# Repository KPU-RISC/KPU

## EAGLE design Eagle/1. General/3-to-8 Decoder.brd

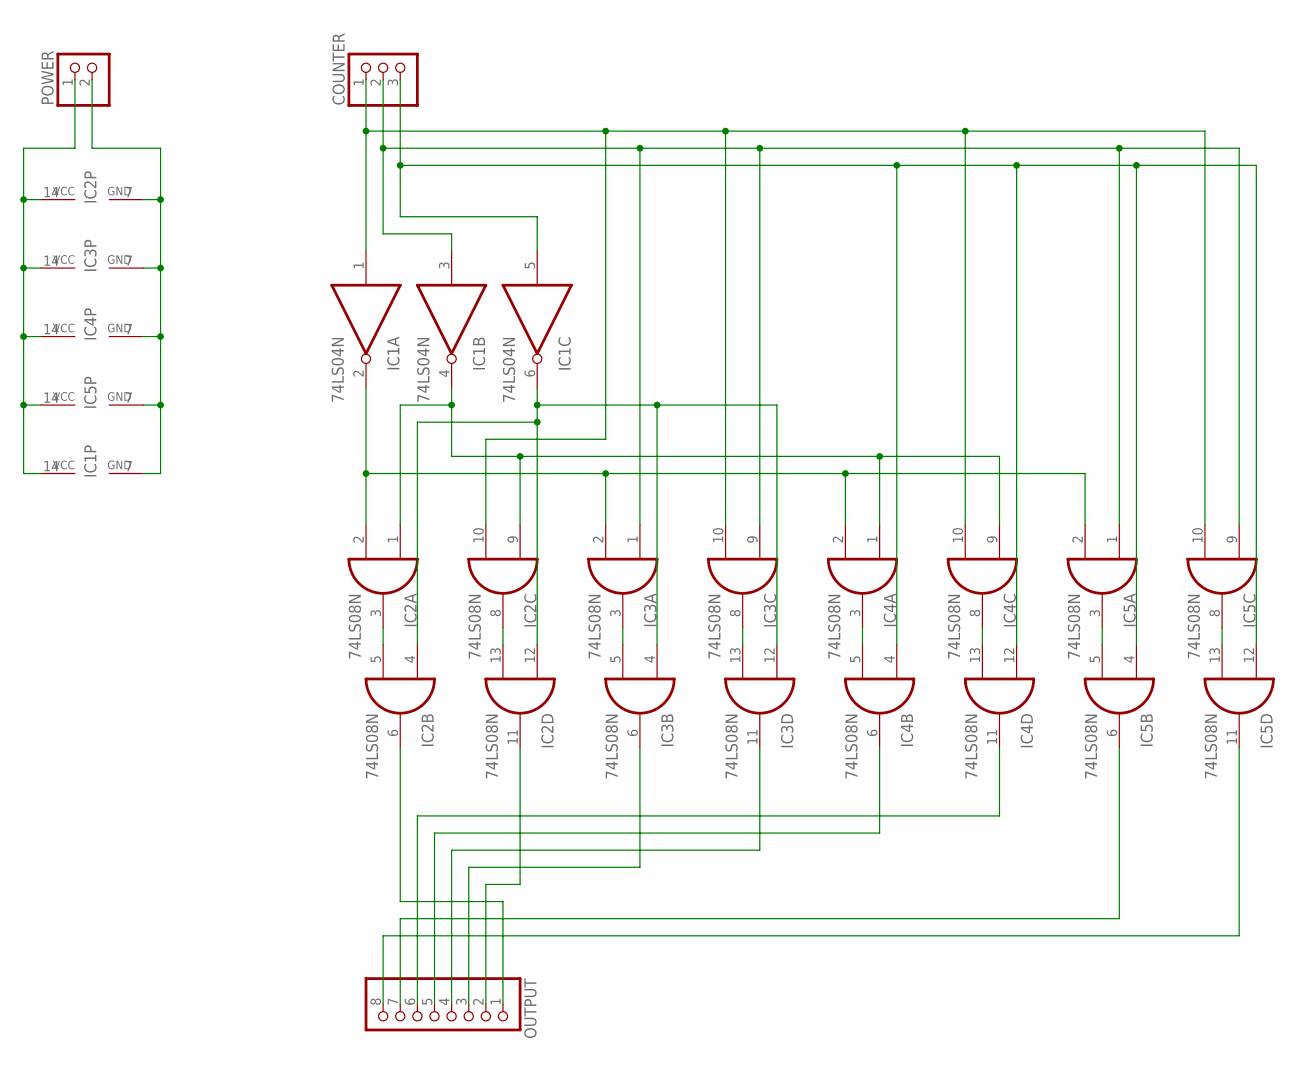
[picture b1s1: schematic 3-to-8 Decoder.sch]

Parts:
COUNTER: PINHD-1X3; 1X03
IC1: 74LS04N; DIL14
IC2, IC3, IC4, IC5: 74LS08N; DIL14
OUTPUT: PINHD-1X8; 1X08
POWER: PINHD-1X2; 1X02

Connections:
GND: IC1.7 (GND), IC2.7 (GND), IC3.7 (GND), IC4.7 (GND), IC5.7 (GND), POWER.2
unnamed: COUNTER.1, IC1.1 (I), IC2.10 (I1), IC3.10 (I1), IC4.10 (I1), IC5.10 (I1)
unnamed: COUNTER.2, IC1.3 (I), IC3.1 (I0), IC3.9 (I0), IC5.1 (I0), IC5.9 (I0)
unnamed: COUNTER.3, IC1.5 (I), IC4.4 (I0), IC4.12 (I0), IC5.4 (I0), IC5.12 (I0)
unnamed: IC1.2 (O), IC2.2 (I1), IC3.2 (I1), IC4.2 (I1), IC5.2 (I1)
unnamed: IC1.4 (O), IC2.1 (I0), IC2.9 (I0), IC4.1 (I0), IC4.9 (I0)
unnamed: IC2.3 (O), IC2.5 (I1)
unnamed: IC1.6 (O), IC2.4 (I0), IC2.12 (I0), IC3.4 (I0), IC3.12 (I0)
unnamed: IC2.11 (O), OUTPUT.2
unnamed: IC2.8 (O), IC2.13 (I1)
unnamed: IC2.6 (O), OUTPUT.1
unnamed: IC3.3 (O), IC3.5 (I1)
unnamed: IC3.6 (O), OUTPUT.3
unnamed: IC3.8 (O), IC3.13 (I1)
unnamed: IC3.11 (O), OUTPUT.4
unnamed: IC4.3 (O), IC4.5 (I1)
unnamed: IC4.6 (O), OUTPUT.5
unnamed: IC4.8 (O), IC4.13 (I1)
unnamed: IC4.11 (O), OUTPUT.6
unnamed: IC5.3 (O), IC5.5 (I1)
unnamed: IC5.6 (O), OUTPUT.7
unnamed: IC5.8 (O), IC5.13 (I1)
unnamed: IC5.11 (O), OUTPUT.8
VCC: IC1.14 (VCC), IC2.14 (VCC), IC3.14 (VCC), IC4.14 (VCC), IC5.14 (VCC), POWER.1

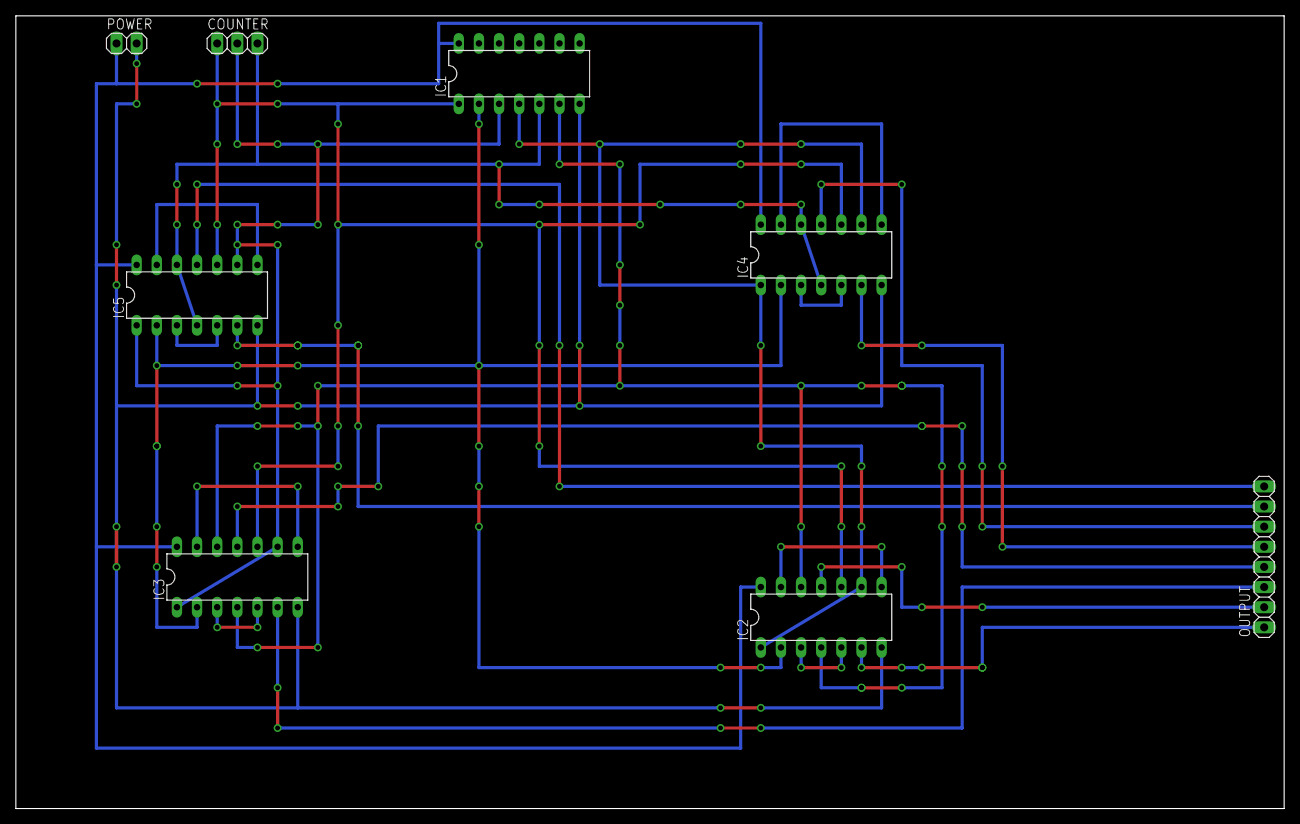
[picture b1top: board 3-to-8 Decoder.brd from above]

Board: 2 copper layers, 160.0 x 100.0 mm, 8 parts (0 on the bottom side), 24 nets.

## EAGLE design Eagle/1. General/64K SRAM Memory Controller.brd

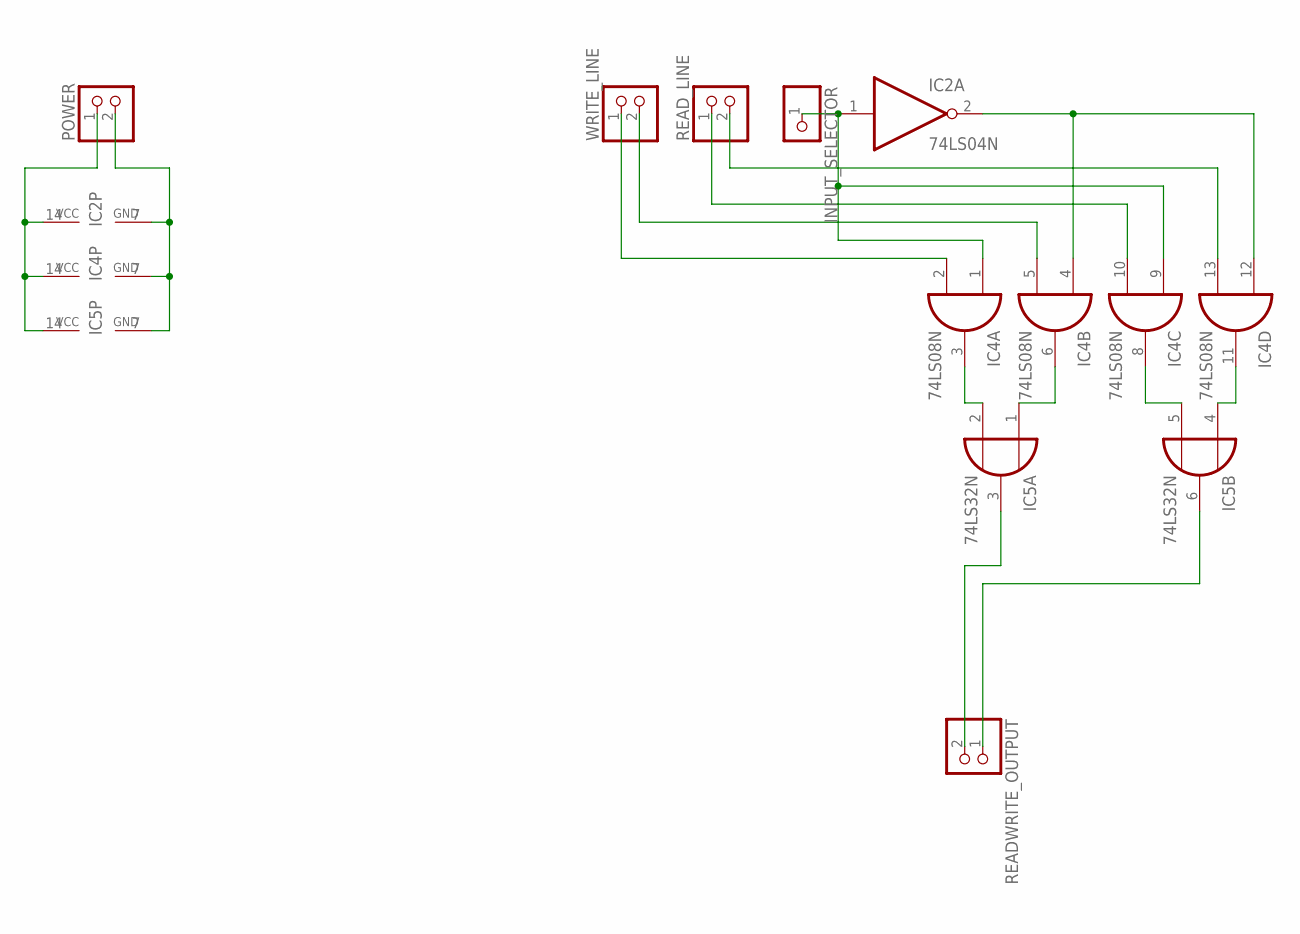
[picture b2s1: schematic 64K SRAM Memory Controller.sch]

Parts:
IC2: 74LS04N; DIL14
IC4: 74LS08N; DIL14
IC5: 74LS32N; DIL14
INPUT_SELECTOR: PINHD-1X1; 1X01
POWER: PINHD-1X2; 1X02
READWRITE_OUTPUT: PINHD-1X2; 1X02
READ_LINE: PINHD-1X2; 1X02
WRITE_LINE: PINHD-1X2; 1X02

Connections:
GND: IC2.7 (GND), IC4.7 (GND), IC5.7 (GND), POWER.2
unnamed: IC2.1 (I), IC4.1 (I0), IC4.9 (I0), INPUT_SELECTOR.1
unnamed: IC5.6 (O), READWRITE_OUTPUT.1
unnamed: IC4.2 (I1), WRITE_LINE.1
unnamed: IC4.5 (I1), WRITE_LINE.2
unnamed: IC2.2 (O), IC4.4 (I0), IC4.12 (I0)
unnamed: IC5.3 (O), READWRITE_OUTPUT.2
unnamed: IC4.10 (I1), READ_LINE.1
unnamed: IC4.13 (I1), READ_LINE.2
unnamed: IC4.3 (O), IC5.2 (I1)
unnamed: IC4.6 (O), IC5.1 (I0)
unnamed: IC4.8 (O), IC5.5 (I1)
unnamed: IC4.11 (O), IC5.4 (I0)
VCC: IC2.14 (VCC), IC4.14 (VCC), IC5.14 (VCC), POWER.1

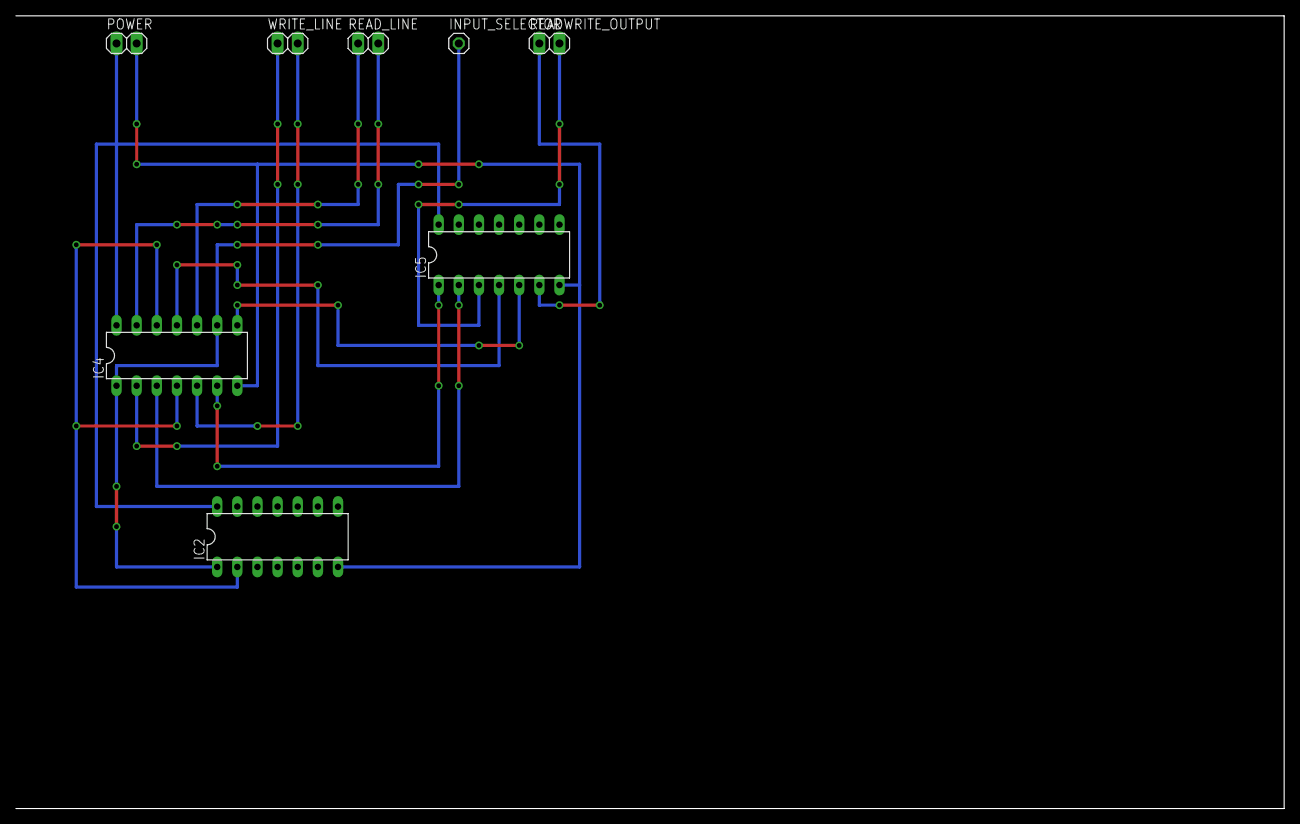
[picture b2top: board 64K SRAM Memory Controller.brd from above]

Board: 2 copper layers, 160.0 x 100.0 mm, 8 parts (0 on the bottom side), 14 nets.

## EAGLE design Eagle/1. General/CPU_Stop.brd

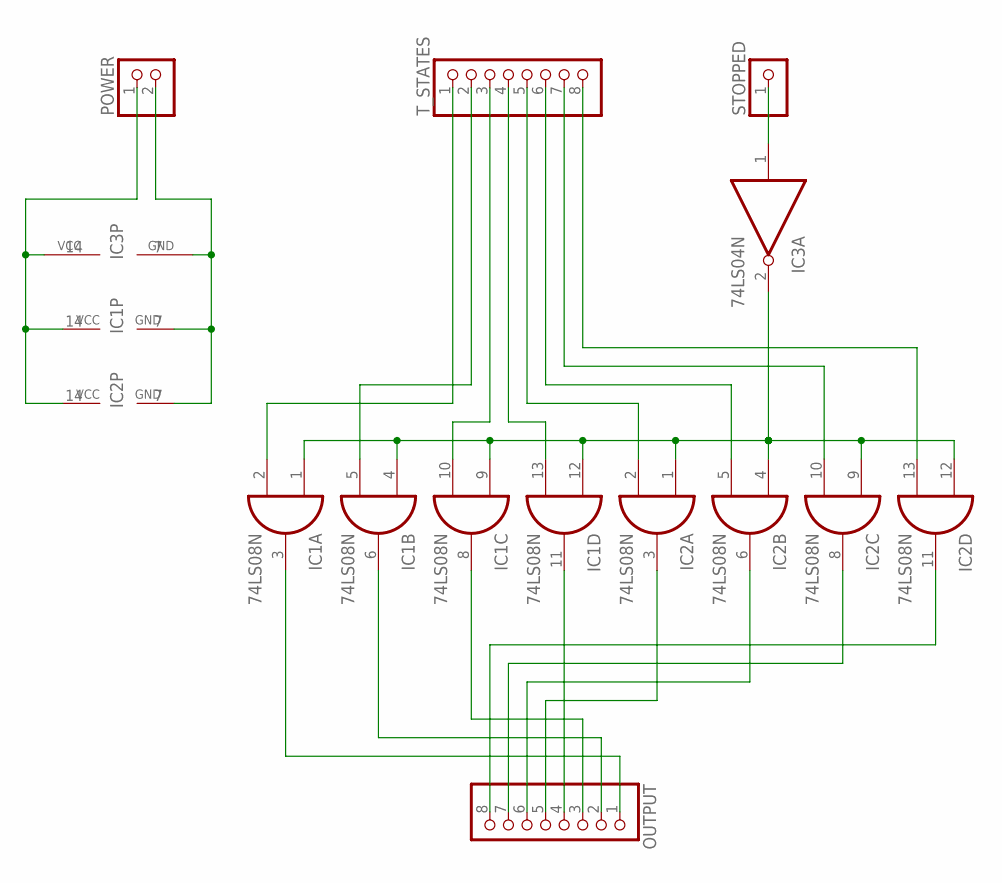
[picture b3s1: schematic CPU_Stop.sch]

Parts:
IC1, IC2: 74LS08N; DIL14
IC3: 74LS04N; DIL14
OUTPUT: PINHD-1X8; 1X08
POWER: PINHD-1X2; 1X02
STOPPED: PINHD-1X1; 1X01
T_STATES: PINHD-1X8; 1X08

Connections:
GND: IC1.7 (GND), IC2.7 (GND), IC3.7 (GND), POWER.2
unnamed: IC3.1 (I), STOPPED.1
unnamed: IC1.1 (I0), IC1.4 (I0), IC1.9 (I0), IC1.12 (I0), IC2.1 (I0), IC2.4 (I0), IC2.9 (I0), IC2.12 (I0), IC3.2 (O)
unnamed: IC1.2 (I1), T_STATES.1
unnamed: IC1.5 (I1), T_STATES.2
unnamed: IC1.10 (I1), T_STATES.3
unnamed: IC1.13 (I1), T_STATES.4
unnamed: IC2.2 (I1), T_STATES.5
unnamed: IC2.5 (I1), T_STATES.6
unnamed: IC2.10 (I1), T_STATES.7
unnamed: IC2.13 (I1), T_STATES.8
unnamed: IC1.3 (O), OUTPUT.1
unnamed: IC1.6 (O), OUTPUT.2
unnamed: IC1.8 (O), OUTPUT.3
unnamed: IC1.11 (O), OUTPUT.4
unnamed: IC2.3 (O), OUTPUT.5
unnamed: IC2.6 (O), OUTPUT.6
unnamed: IC2.8 (O), OUTPUT.7
unnamed: IC2.11 (O), OUTPUT.8
VCC: IC1.14 (VCC), IC2.14 (VCC), IC3.14 (VCC), POWER.1

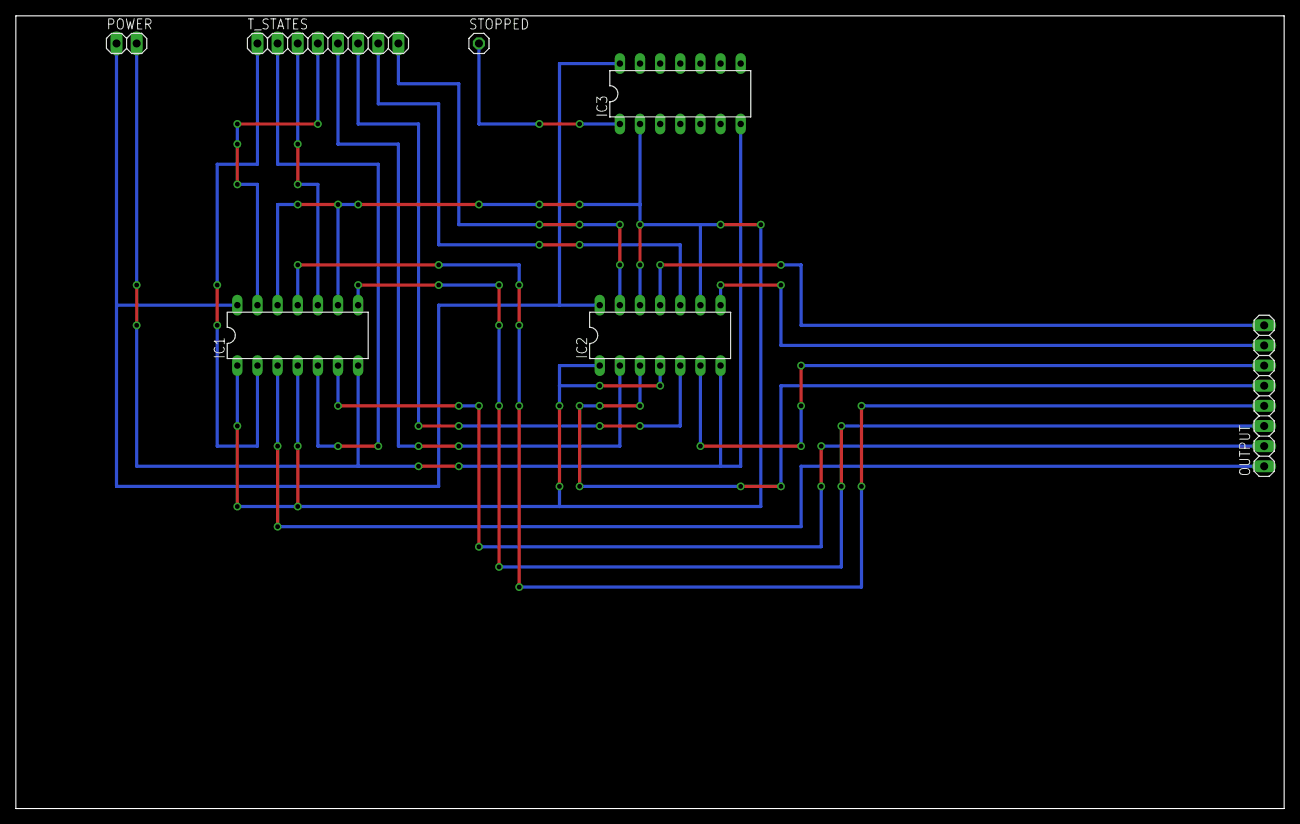
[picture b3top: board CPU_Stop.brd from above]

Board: 2 copper layers, 160.0 x 100.0 mm, 7 parts (0 on the bottom side), 20 nets.

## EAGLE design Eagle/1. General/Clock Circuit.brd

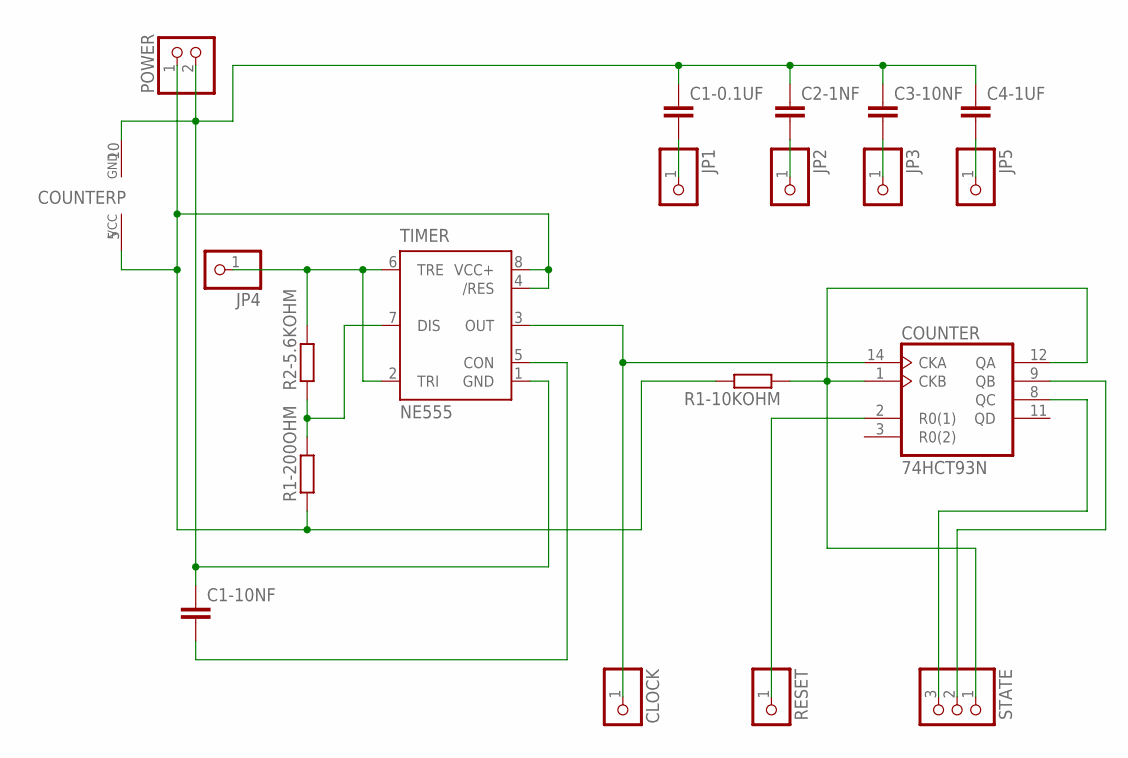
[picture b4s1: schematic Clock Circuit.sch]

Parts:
C1-0.1UF, C1-10NF, C2-1NF, C3-10NF, C4-1UF: C-EU050-025X075; C050-025X075
CLOCK: PINHD-1X1; 1X01
COUNTER: 74HCT93N; DIL14
JP1, JP2, JP3, JP4, JP5: PINHD-1X1; 1X01
POWER: PINHD-1X2; 1X02
R1-10KOHM, R1-200OHM, R2-5.6KOHM: R-EU_0207/10; 0207/10
RESET: PINHD-1X1; 1X01
STATE: PINHD-1X3; 1X03
TIMER: NE555; DIL-08

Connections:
GND: C1-0.1UF.1, C1-10NF.1, C2-1NF.1, C3-10NF.1, C4-1UF.1, COUNTER.10 (GND), POWER.2, TIMER.1 (GND)
unnamed: CLOCK.1, COUNTER.14 (CKA), TIMER.3 (OUT)
unnamed: JP4.1, R2-5.6KOHM.2, TIMER.2 (TRI), TIMER.6 (TRE)
unnamed: COUNTER.1 (CKB), COUNTER.12 (QA), R1-10KOHM.1, STATE.1
unnamed: COUNTER.2 (R0(1)), RESET.1
unnamed: COUNTER.8 (QC), STATE.3
unnamed: COUNTER.9 (QB), STATE.2
unnamed: C1-10NF.2, TIMER.5 (CON)
unnamed: C1-0.1UF.2, JP1.1
unnamed: C2-1NF.2, JP2.1
unnamed: C3-10NF.2, JP3.1
unnamed: C4-1UF.2, JP5.1
unnamed: R1-200OHM.2, R2-5.6KOHM.1, TIMER.7 (DIS)
VCC: COUNTER.5 (VCC), POWER.1, R1-10KOHM.2, R1-200OHM.1, TIMER.4 (/RES), TIMER.8 (VCC+)

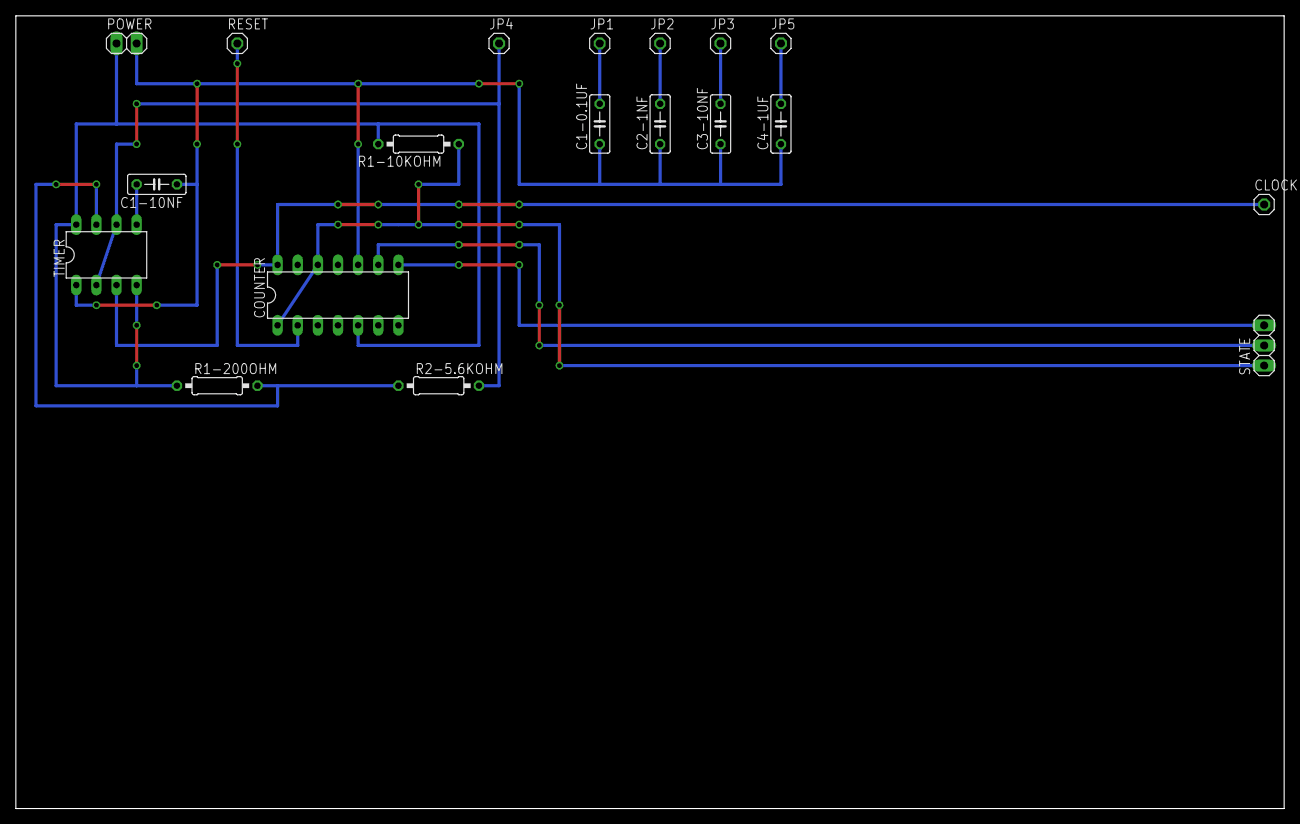
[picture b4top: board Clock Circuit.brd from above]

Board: 2 copper layers, 160.0 x 100.0 mm, 19 parts (0 on the bottom side), 14 nets.

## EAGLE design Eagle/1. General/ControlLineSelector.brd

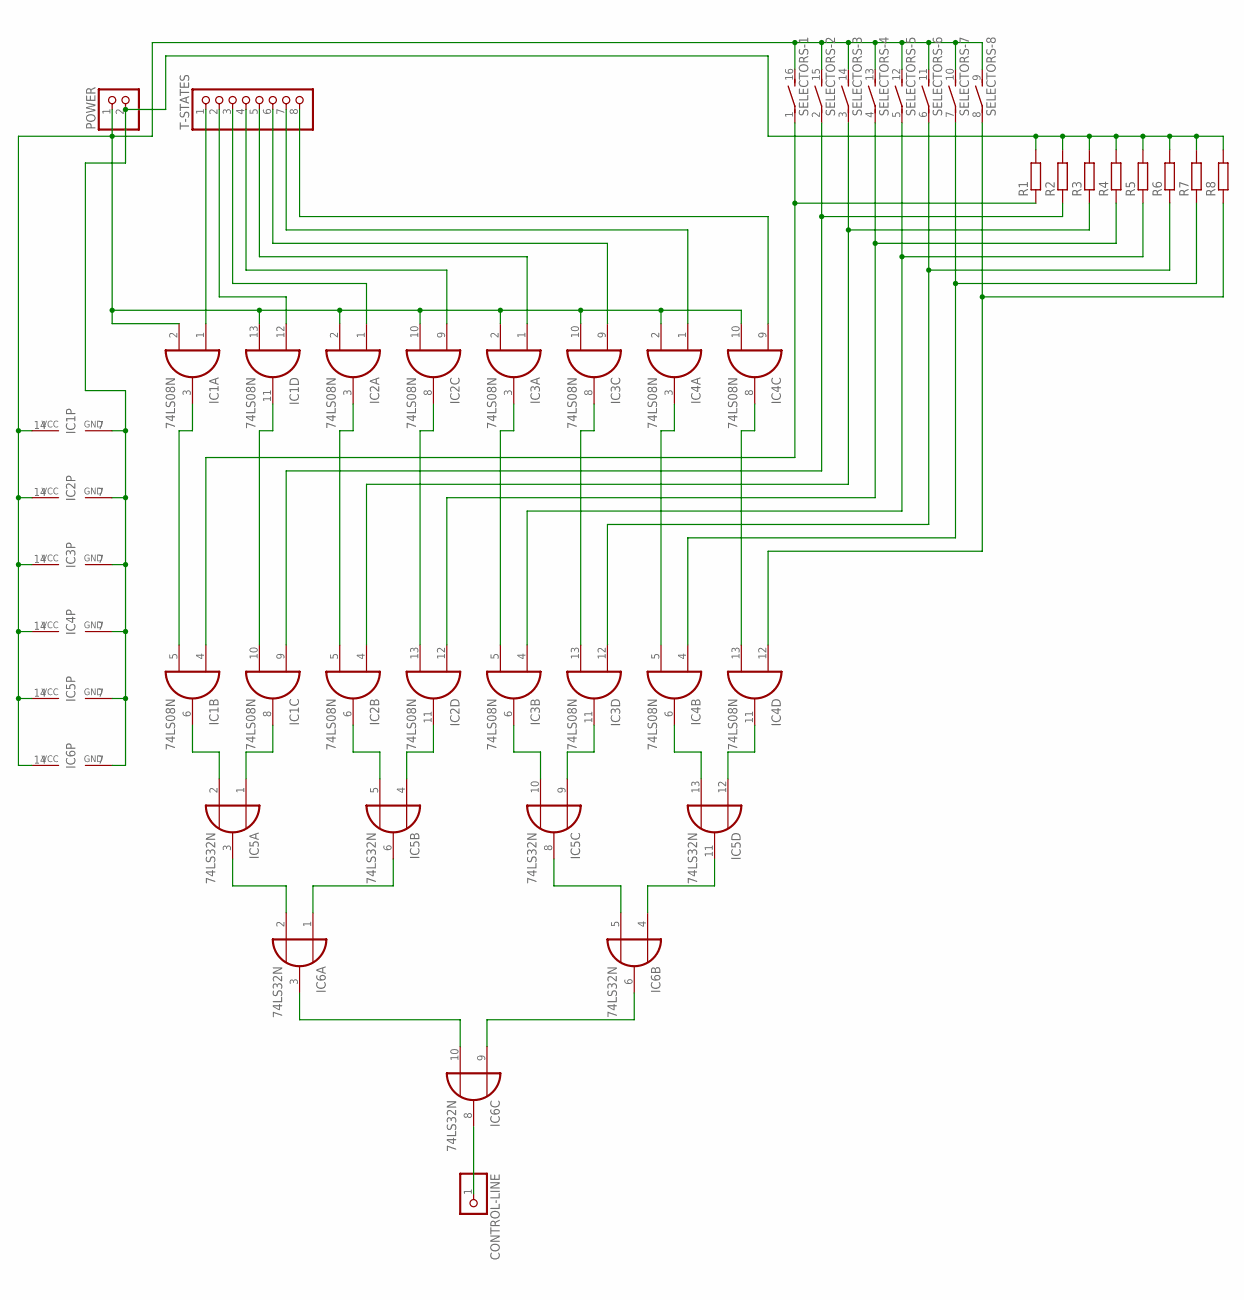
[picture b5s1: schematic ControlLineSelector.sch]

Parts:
CONTROL-LINE: PINHD-1X1; 1X01
IC1, IC2, IC3, IC4: 74LS08N; DIL14
IC5, IC6: 74LS32N; DIL14
POWER: PINHD-1X2; 1X02
R1, R2, R3, R4, R5, R6, R7, R8: R-EU_0207/7; 0207/7
SELECTORS: DIP08S
T-STATES: PINHD-1X8; 1X08

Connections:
GND: IC1.7 (GND), IC2.7 (GND), IC3.7 (GND), IC4.7 (GND), IC5.7 (GND), IC6.7 (GND), POWER.2, R1.2, R2.2, R3.2, R4.2, R5.2, R6.2, R7.2, R8.2
unnamed: IC1.3 (O), IC1.5 (I1)
unnamed: IC1.1 (I0), T-STATES.1
unnamed: IC1.4 (I0), R1.1, SELECTORS.1
unnamed: IC1.12 (I0), T-STATES.2
unnamed: IC4.1 (I0), T-STATES.7
unnamed: IC1.10 (I1), IC1.11 (O)
unnamed: IC1.9 (I0), R2.1, SELECTORS.2 (1)
unnamed: IC4.9 (I0), T-STATES.8
unnamed: IC2.3 (O), IC2.5 (I1)
unnamed: IC2.8 (O), IC2.13 (I1)
unnamed: IC3.3 (O), IC3.5 (I1)
unnamed: IC2.1 (I0), T-STATES.3
unnamed: IC2.9 (I0), T-STATES.4
unnamed: IC3.1 (I0), T-STATES.5
unnamed: IC3.9 (I0), T-STATES.6
unnamed: IC3.8 (O), IC3.13 (I1)
unnamed: IC4.3 (O), IC4.5 (I1)
unnamed: IC4.8 (O), IC4.13 (I1)
unnamed: IC2.4 (I0), R3.1, SELECTORS.3 (1)
unnamed: IC3.4 (I0), R5.1, SELECTORS.5 (1)
unnamed: IC3.12 (I0), R6.1, SELECTORS.6 (1)
unnamed: IC4.4 (I0), R7.1, SELECTORS.7 (1)
unnamed: IC4.12 (I0), R8.1, SELECTORS.8 (1)
unnamed: IC1.6 (O), IC5.2 (I1)
unnamed: IC1.8 (O), IC5.1 (I0)
unnamed: IC2.6 (O), IC5.5 (I1)
unnamed: IC2.11 (O), IC5.4 (I0)
unnamed: IC3.6 (O), IC5.10 (I1)
unnamed: IC3.11 (O), IC5.9 (I0)
unnamed: IC4.6 (O), IC5.13 (I1)
unnamed: IC4.11 (O), IC5.12 (I0)
unnamed: IC5.3 (O), IC6.2 (I1)
unnamed: IC5.6 (O), IC6.1 (I0)
unnamed: IC5.8 (O), IC6.5 (I1)
unnamed: IC5.11 (O), IC6.4 (I0)
unnamed: IC6.3 (O), IC6.10 (I1)
unnamed: IC6.6 (O), IC6.9 (I0)
unnamed: CONTROL-LINE.1, IC6.8 (O)
unnamed: IC2.12 (I0), R4.1, SELECTORS.4 (1)
VCC: IC1.2 (I1), IC1.13 (I1), IC1.14 (VCC), IC2.2 (I1), IC2.10 (I1), IC2.14 (VCC), IC3.2 (I1), IC3.10 (I1), IC3.14 (VCC), IC4.2 (I1), IC4.10 (I1), IC4.14 (VCC), IC5.14 (VCC), IC6.14 (VCC), POWER.1, SELECTORS.9 (2), SELECTORS.10 (2), SELECTORS.11 (2), SELECTORS.12 (2), SELECTORS.13 (2), SELECTORS.14 (2), SELECTORS.15 (2), SELECTORS.16 (2)

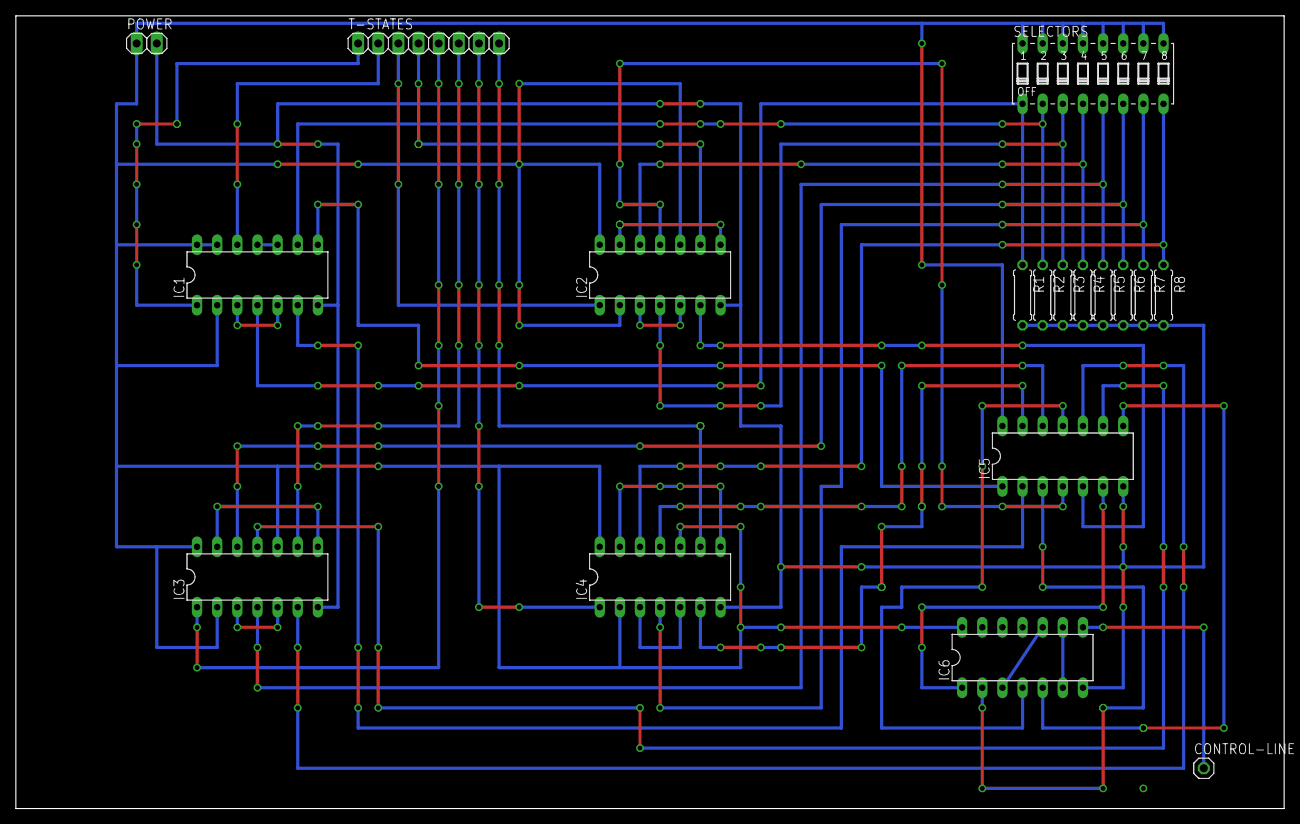
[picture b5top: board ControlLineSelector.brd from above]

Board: 2 copper layers, 160.0 x 100.0 mm, 18 parts (0 on the bottom side), 41 nets.

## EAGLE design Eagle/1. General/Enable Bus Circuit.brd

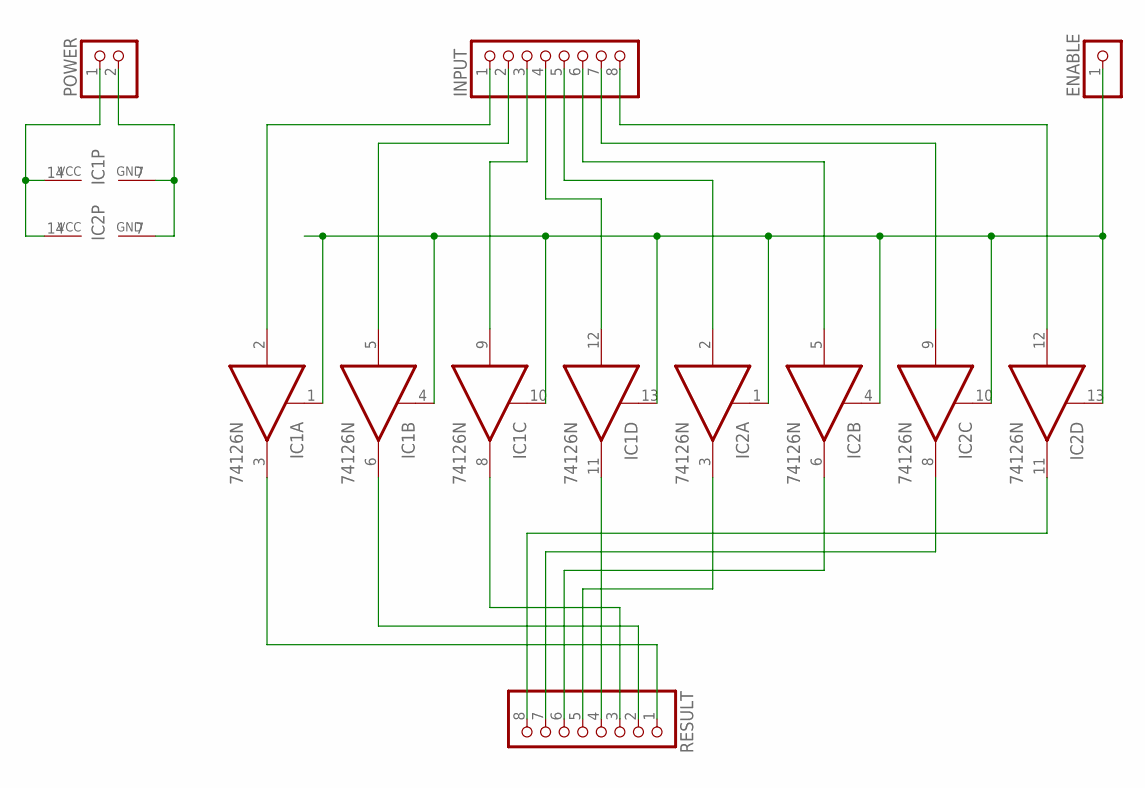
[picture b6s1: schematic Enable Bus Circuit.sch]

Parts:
ENABLE: PINHD-1X1; 1X01
IC1, IC2: 74126N; DIL14
INPUT: PINHD-1X8; 1X08
POWER: PINHD-1X2; 1X02
RESULT: PINHD-1X8; 1X08

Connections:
GND: IC1.7 (GND), IC2.7 (GND), POWER.2
unnamed: IC1.2 (I), INPUT.1
unnamed: IC1.5 (I), INPUT.2
unnamed: IC1.9 (I), INPUT.3
unnamed: IC1.12 (I), INPUT.4
unnamed: IC2.2 (I), INPUT.5
unnamed: IC2.5 (I), INPUT.6
unnamed: IC2.9 (I), INPUT.7
unnamed: IC2.12 (I), INPUT.8
unnamed: ENABLE.1, IC1.1 (OE), IC1.4 (OE), IC1.10 (OE), IC1.13 (OE), IC2.1 (OE), IC2.4 (OE), IC2.10 (OE), IC2.13 (OE)
unnamed: IC1.3 (O), RESULT.1
unnamed: IC1.6 (O), RESULT.2
unnamed: IC1.8 (O), RESULT.3
unnamed: IC2.11 (O), RESULT.8
unnamed: IC2.3 (O), RESULT.5
unnamed: IC2.6 (O), RESULT.6
unnamed: IC2.8 (O), RESULT.7
unnamed: IC1.11 (O), RESULT.4
VCC: IC1.14 (VCC), IC2.14 (VCC), POWER.1

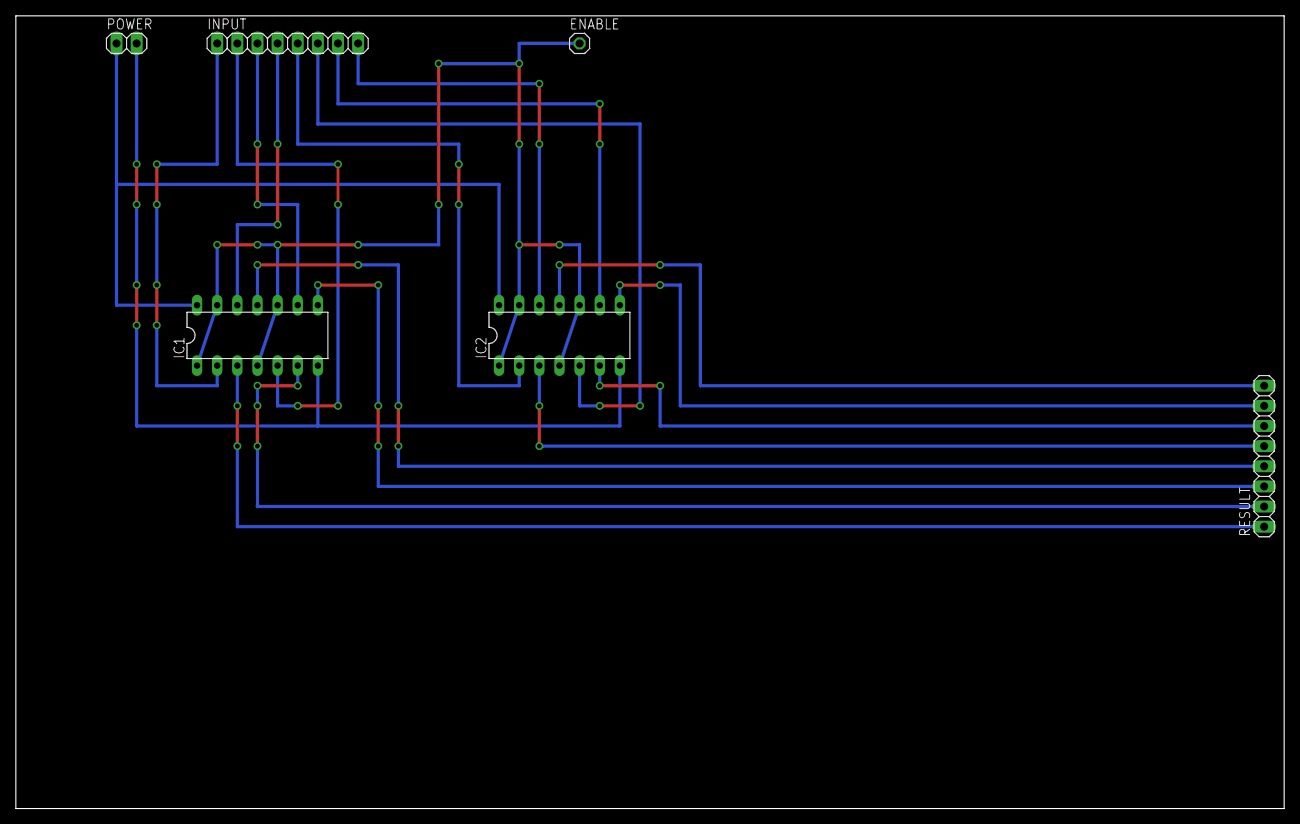
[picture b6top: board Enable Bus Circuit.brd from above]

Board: 2 copper layers, 160.0 x 100.0 mm, 6 parts (0 on the bottom side), 19 nets.

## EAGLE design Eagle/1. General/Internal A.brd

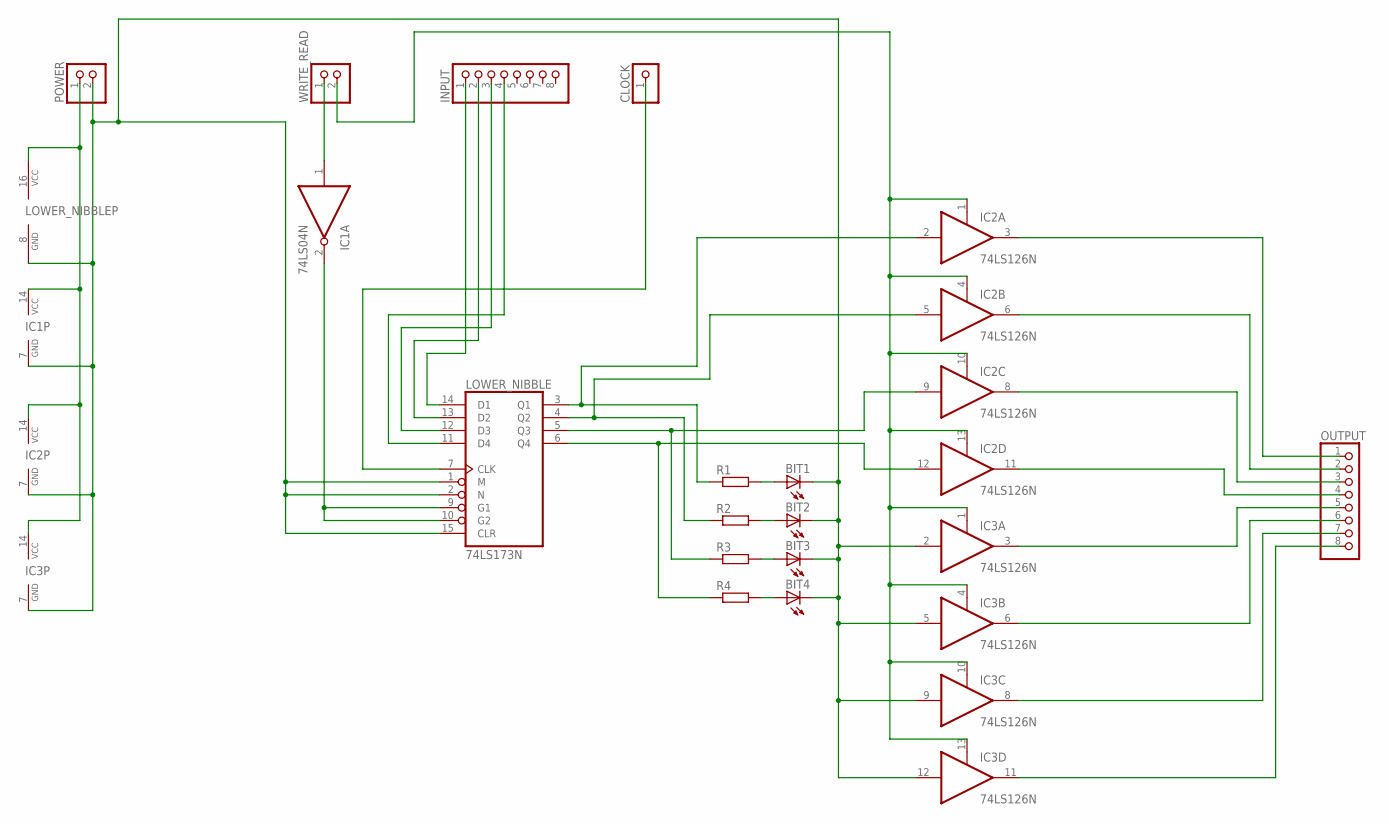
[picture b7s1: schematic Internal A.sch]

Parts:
BIT1, BIT2, BIT3, BIT4: LED3MM
CLOCK: PINHD-1X1; 1X01
IC1: 74LS04N; DIL14
IC2, IC3: 74LS126N; DIL14
INPUT: PINHD-1X8; 1X08
LOWER_NIBBLE: 74LS173N; DIL16
OUTPUT: PINHD-1X8; 1X08
POWER: PINHD-1X2; 1X02
R1, R2, R3, R4: R-EU_0207/10; 0207/10
WRITE_READ: PINHD-1X2; 1X02

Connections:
GND: BIT1.K (C), BIT2.K (C), BIT3.K (C), BIT4.K (C), IC1.7 (GND), IC2.7 (GND), IC3.2 (I), IC3.5 (I), IC3.7 (GND), IC3.9 (I), IC3.12 (I), LOWER_NIBBLE.1 (M), LOWER_NIBBLE.2 (N), LOWER_NIBBLE.8 (GND), LOWER_NIBBLE.15 (CLR), POWER.2
unnamed: IC1.1 (I), WRITE_READ.1
unnamed: BIT1.A, R1.2
unnamed: BIT2.A, R2.2
unnamed: BIT3.A, R3.2
unnamed: BIT4.A, R4.2
unnamed: IC2.11 (O), OUTPUT.4
unnamed: IC1.2 (O), LOWER_NIBBLE.9 (G1), LOWER_NIBBLE.10 (G2)
unnamed: CLOCK.1, LOWER_NIBBLE.7 (CLK)
unnamed: INPUT.1, LOWER_NIBBLE.14 (D1)
unnamed: INPUT.2, LOWER_NIBBLE.13 (D2)
unnamed: INPUT.3, LOWER_NIBBLE.12 (D3)
unnamed: INPUT.4, LOWER_NIBBLE.11 (D4)
unnamed: IC2.2 (I), LOWER_NIBBLE.3 (Q1), R1.1
unnamed: IC2.5 (I), LOWER_NIBBLE.4 (Q2), R2.1
unnamed: IC2.9 (I), LOWER_NIBBLE.5 (Q3), R3.1
unnamed: IC2.12 (I), LOWER_NIBBLE.6 (Q4), R4.1
unnamed: IC2.1 (OE), IC2.4 (OE), IC2.10 (OE), IC2.13 (OE), IC3.1 (OE), IC3.4 (OE), IC3.10 (OE), IC3.13 (OE), WRITE_READ.2
unnamed: IC2.3 (O), OUTPUT.1
unnamed: IC2.6 (O), OUTPUT.2
unnamed: IC2.8 (O), OUTPUT.3
unnamed: IC3.3 (O), OUTPUT.5
unnamed: IC3.6 (O), OUTPUT.6
unnamed: IC3.8 (O), OUTPUT.7
unnamed: IC3.11 (O), OUTPUT.8
VCC: IC1.14 (VCC), IC2.14 (VCC), IC3.14 (VCC), LOWER_NIBBLE.16 (VCC), POWER.1

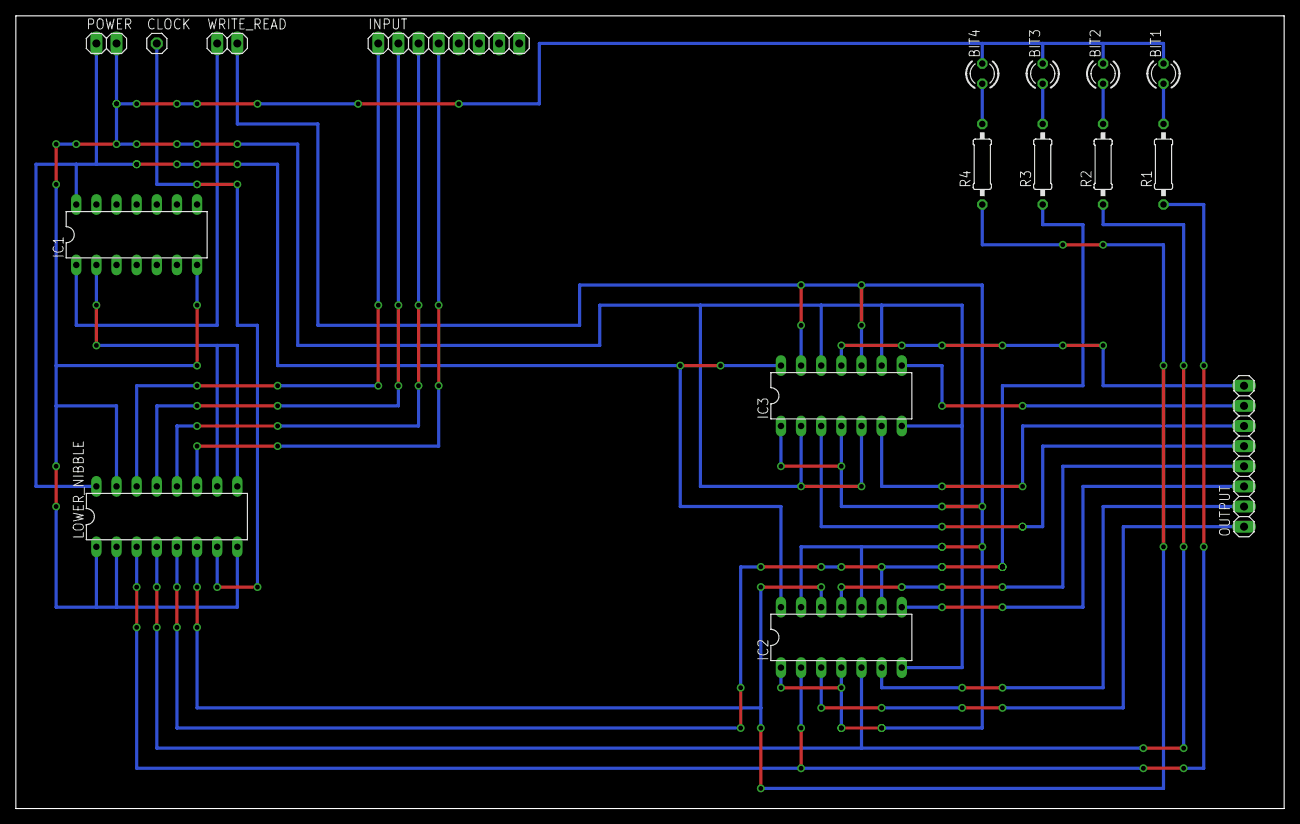
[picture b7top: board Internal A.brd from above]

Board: 2 copper layers, 160.0 x 100.0 mm, 17 parts (0 on the bottom side), 26 nets.
